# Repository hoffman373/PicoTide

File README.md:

# PicoTide

An ISA card that connects a Raspberry Pi Pico to an 8-bit ISA slot, so the Pico can see and drive the bus of a PC/XT-class machine. With the firmware in [`firmware/`](firmware/), the card serves an option ROM, such as the XTIDE Universal BIOS, to the machine.

## Overview

The ISA bus runs at 5 V and the Pico's GPIO is 3.3 V, so every signal between them passes through a level translator.

- **MCU:** Raspberry Pi Pico. The footprint is the Pico W's and takes any Pico-footprint board; the firmware targets the Pico 2 (RP2350).
- **Level translation:** SN74LVC8T245 8-bit dual-supply transceivers (3.3 V Pico side, 5 V ISA side)
- **Glue logic:** 74LVC1G02 / 74LVC1G04 / 74LVC1G06 single gates. The NOR gates combine SMEMR# and SMEMW# with AEN into `VALID_READ` and `VALID_WRITE`.
- **Bus connector:** 8-bit ISA edge connector (`Bus_ISA_8bit`)

### Pin mapping

| Pico GPIO | ISA signal | Net label |
|---|---|---|
| GPIO0-7 | A0-A7 and D0-D7, multiplexed | `P_A0_D0` ... `P_A7_D7` |
| GPIO8-15 | A8-A15 | `P_A8` ... `P_A15` |
| GPIO16-19 | A16-A19 | `P_A16` ... `P_A19` |
| GPIO20 | IO CH RDY (high pulls it low) | `P_IO_CHRDY` |
| GPIO21 | RESET DRV | `P_RESET` |
| GPIO22 | Address/data select | `P_ADR_DATA` |
| GPIO26 | Data translator direction | `P_DATA_DIR` |
| GPIO27 | NOR(SMEMW#, AEN) | `VALID_WRITE` |
| GPIO28 | NOR(SMEMR#, AEN) | `VALID_READ` |

Address and data share GPIO0-7. Each of those GPIOs goes through one translator to the matching address line and through another to the matching data line. `P_ADR_DATA` picks which translator owns them: high enables the address translator, low enables the data translator, and `P_DATA_DIR` then sets whether data flows from the Pico to the bus or the other way.

`IO_CHRDY` (ISA IO CH RDY) is driven through a 74LVC1G06 open-drain output so the Pico can insert wait states without driving the line high.

Net labels use a `P_` prefix for the Pico side of a translator. The matching ISA-side labels carry the bare ISA name.

## Opening the project

1. Install [KiCad](https://www.kicad.org/) 10 or newer. The files use the KiCad 10 format and will not open in older versions.
2. Clone the repository:
   ```
   git clone https://github.com/hoffman373/PicoTide.git
   ```
3. Open `PicoTide.kicad_pro`.

Custom footprints live in `lib/footprints/` and are registered through the project's `fp-lib-table` using `${KIPRJMOD}`, so no library setup is needed. Everything else uses stock KiCad symbols and footprints.

## Firmware

The [`firmware/`](firmware/) directory builds three firmwares for the card: a bench tester for a newly built card, a bus logger that shows where a BIOS scans for option ROMs, and an option ROM server. See [`firmware/README.md`](firmware/README.md) for building and using them.

## Notes

- **Bus timing:** at 4.77 MHz, a Pico 2 polling the bus from RAM on its second core answers memory reads in software with time to spare, without PIO or wait states. The option ROM server has booted an XT from the XTIDE Universal BIOS this way. `IO_CHRDY` is there for faster machines or slower responses.

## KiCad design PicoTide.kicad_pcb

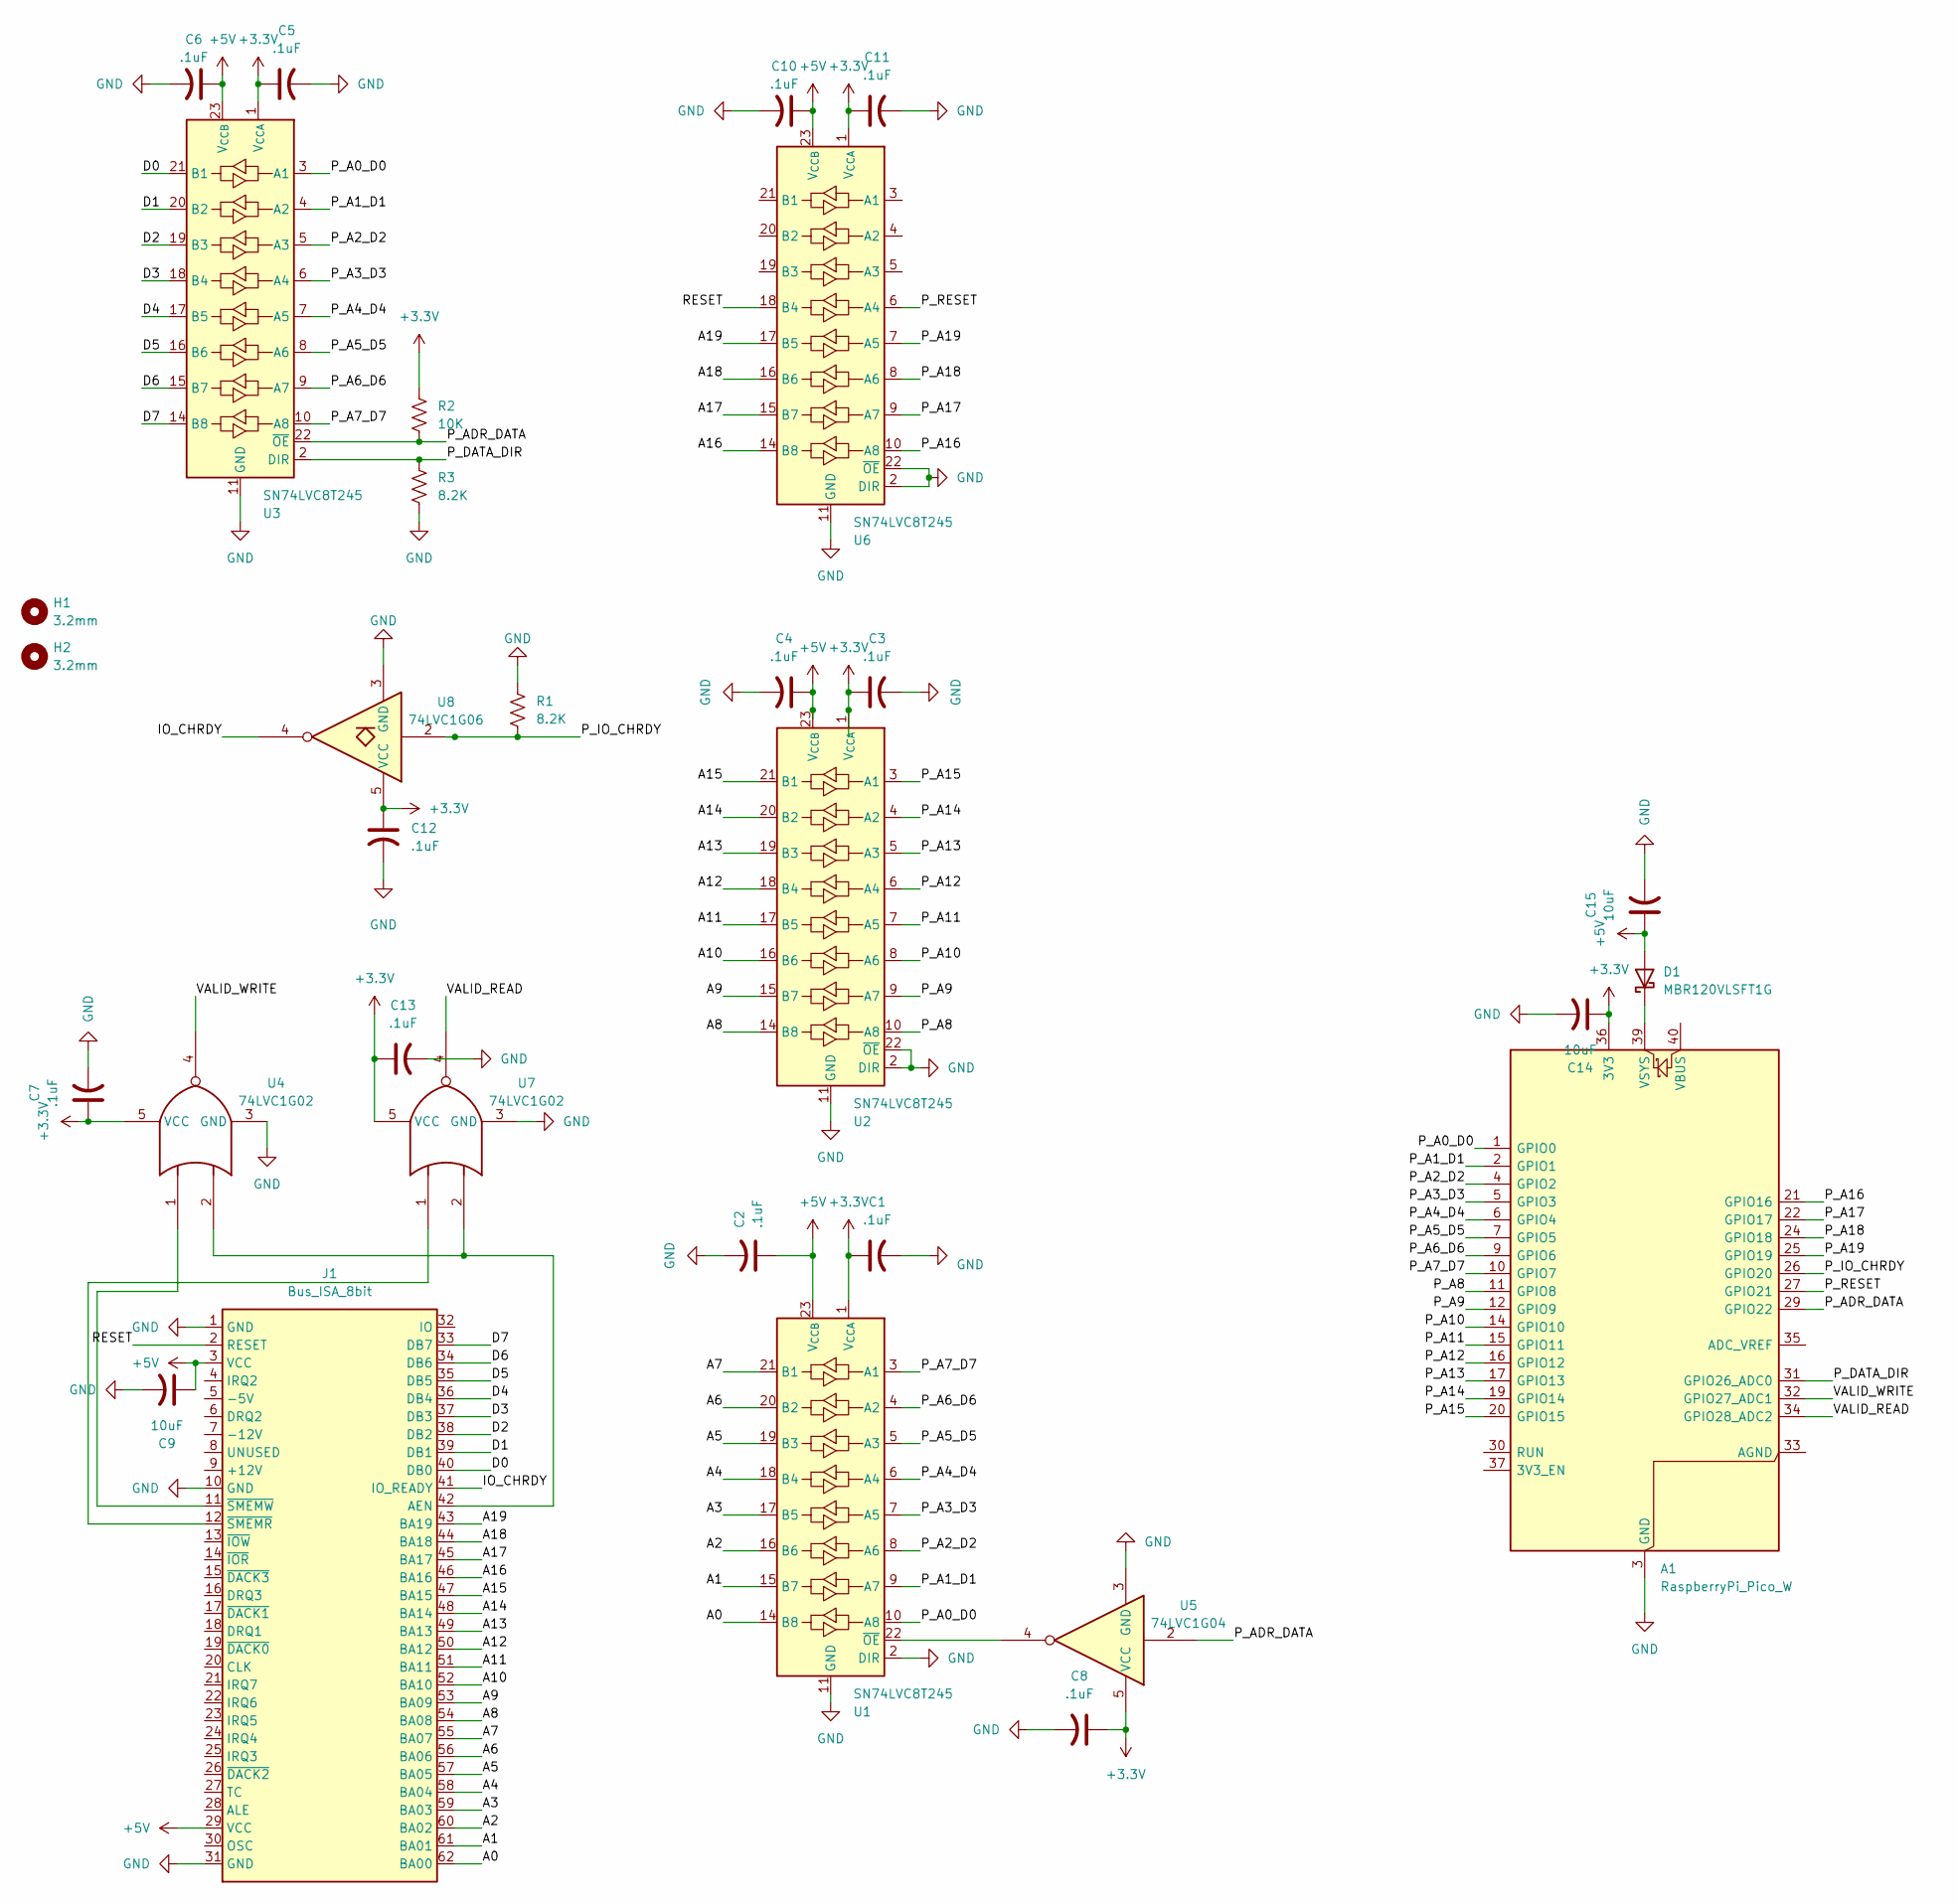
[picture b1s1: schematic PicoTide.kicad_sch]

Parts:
A1: RaspberryPi_Pico_W; RaspberryPi_Pico_MountingHole
C1, C2, C3, C4, C5, C6, C7, C8, C10, C11, C12, C13: .1uF; C_0805_2012Metric_Pad1.18x1.45mm_HandSolder
C9, C14, C15: 10uF; C_1206_3216Metric_Pad1.33x1.80mm_HandSolder
D1: MBR120VLSFT1G; D_SOD-123F
H1, H2: 3.2mm; MountingHole_3.2mm_M3
J1: Bus_ISA_8bit; PC_AT_8BIT
R1, R3: 8.2K; R_0805_2012Metric_Pad1.20x1.40mm_HandSolder
R2: 10K; R_0805_2012Metric_Pad1.20x1.40mm_HandSolder
U1, U2, U3, U6: SN74LVC8T245; SOIC-24W_7.5x15.4mm_P1.27mm
U4, U7: 74LVC1G02; SOT-23-5_HandSoldering
U5: 74LVC1G04; SOT-23-5_HandSoldering
U8: 74LVC1G06; SOT-23-5_HandSoldering

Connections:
+3.3V: A1.36 (3V3), C1.1, C3.1, C5.1, C7.1, C8.1, C11.1, C12.1, C13.1, C14.1, R2.1, U1.1 (V_{CCA}), U2.1 (V_{CCA}), U3.1 (V_{CCA}), U4.5 (VCC), U5.5 (VCC), U6.1 (V_{CCA}), U7.5 (VCC), U8.5 (VCC)
+5V: C2.1, C4.1, C6.1, C9.1, C10.1, C15.1, D1.2 (A), J1.3 (VCC), J1.29 (VCC), U1.23 (V_{CCB}), U1.24 (V_{CCB}), U2.23 (V_{CCB}), U2.24 (V_{CCB}), U3.23 (V_{CCB}), U3.24 (V_{CCB}), U6.23 (V_{CCB}), U6.24 (V_{CCB})
/A0: J1.62 (BA00), U1.14 (B8)
/A1: J1.61 (BA01), U1.15 (B7)
/A2: J1.60 (BA02), U1.16 (B6)
/A3: J1.59 (BA03), U1.17 (B5)
/A4: J1.58 (BA04), U1.18 (B4)
/A5: J1.57 (BA05), U1.19 (B3)
/A6: J1.56 (BA06), U1.20 (B2)
/A7: J1.55 (BA07), U1.21 (B1)
/A8: J1.54 (BA08), U2.14 (B8)
/A9: J1.53 (BA09), U2.15 (B7)
/A10: J1.52 (BA10), U2.16 (B6)
/A11: J1.51 (BA11), U2.17 (B5)
/A12: J1.50 (BA12), U2.18 (B4)
/A13: J1.49 (BA13), U2.19 (B3)
/A14: J1.48 (BA14), U2.20 (B2)
/A15: J1.47 (BA15), U2.21 (B1)
/A16: J1.46 (BA16), U6.14 (B8)
/A17: J1.45 (BA17), U6.15 (B7)
/A18: J1.44 (BA18), U6.16 (B6)
/A19: J1.43 (BA19), U6.17 (B5)
/D0: J1.40 (DB0), U3.21 (B1)
/D1: J1.39 (DB1), U3.20 (B2)
/D2: J1.38 (DB2), U3.19 (B3)
/D3: J1.37 (DB3), U3.18 (B4)
/D4: J1.36 (DB4), U3.17 (B5)
/D5: J1.35 (DB5), U3.16 (B6)
/D6: J1.34 (DB6), U3.15 (B7)
/D7: J1.33 (DB7), U3.14 (B8)
/IO_CHRDY: J1.41 (IO_READY), U8.4
/P_A0_D0: A1.1 (GPIO0), U1.10 (A8), U3.3 (A1)
/P_A1_D1: A1.2 (GPIO1), U1.9 (A7), U3.4 (A2)
/P_A2_D2: A1.4 (GPIO2), U1.8 (A6), U3.5 (A3)
/P_A3_D3: A1.5 (GPIO3), U1.7 (A5), U3.6 (A4)
/P_A4_D4: A1.6 (GPIO4), U1.6 (A4), U3.7 (A5)
/P_A5_D5: A1.7 (GPIO5), U1.5 (A3), U3.8 (A6)
/P_A6_D6: A1.9 (GPIO6), U1.4 (A2), U3.9 (A7)
/P_A7_D7: A1.10 (GPIO7), U1.3 (A1), U3.10 (A8)
/P_A8: A1.11 (GPIO8), U2.10 (A8)
/P_A9: A1.12 (GPIO9), U2.9 (A7)
/P_A10: A1.14 (GPIO10), U2.8 (A6)
/P_A11: A1.15 (GPIO11), U2.7 (A5)
/P_A12: A1.16 (GPIO12), U2.6 (A4)
/P_A13: A1.17 (GPIO13), U2.5 (A3)
/P_A14: A1.19 (GPIO14), U2.4 (A2)
/P_A15: A1.20 (GPIO15), U2.3 (A1)
/P_A16: A1.21 (GPIO16), U6.10 (A8)
/P_A17: A1.22 (GPIO17), U6.9 (A7)
/P_A18: A1.24 (GPIO18), U6.8 (A6)
/P_A19: A1.25 (GPIO19), U6.7 (A5)
/P_ADR_DATA: A1.29 (GPIO22), R2.2, U3.22 (~OE), U5.2
/P_DATA_DIR: A1.31 (GPIO26_ADC0), R3.1, U3.2 (DIR)
/P_IO_CHRDY: A1.26 (GPIO20), R1.2, U8.2
/P_RESET: A1.27 (GPIO21), U6.6 (A4)
/RESET: J1.2 (RESET), U6.18 (B4)
/VALID_READ: A1.34 (GPIO28_ADC2), U7.4
/VALID_WRITE: A1.32 (GPIO27_ADC1), U4.4
GND: A1.3 (GND), A1.8 (GND), A1.13 (GND), A1.18 (GND), A1.23 (GND), A1.28 (GND), A1.38 (GND), C1.2, C2.2, C3.2, C4.2, C5.2, C6.2, C7.2, C8.2, C9.2, C10.2, C11.2, C12.2, C13.2, C14.2, C15.2, J1.1 (GND), J1.10 (GND), J1.31 (GND), R1.1, R3.2, U1.2 (DIR), U1.11 (GND), U1.12 (GND), U1.13 (GND), U2.2 (DIR), U2.11 (GND), U2.12 (GND), U2.13 (GND), U2.22 (~OE), U3.11 (GND), U3.12 (GND), U3.13 (GND), U4.3 (GND), U5.3 (GND), U6.2 (DIR), U6.11 (GND), U6.12 (GND), U6.13 (GND), U6.22 (~OE), U7.3 (GND), U8.3 (GND)
unnamed: A1.39 (VSYS), D1.1 (K)
unnamed: J1.42 (AEN), U4.2, U7.2
unnamed: J1.12 (~SMEMR), U7.1
unnamed: J1.11 (~SMEMW), U4.1
unnamed: U1.22 (~OE), U5.4

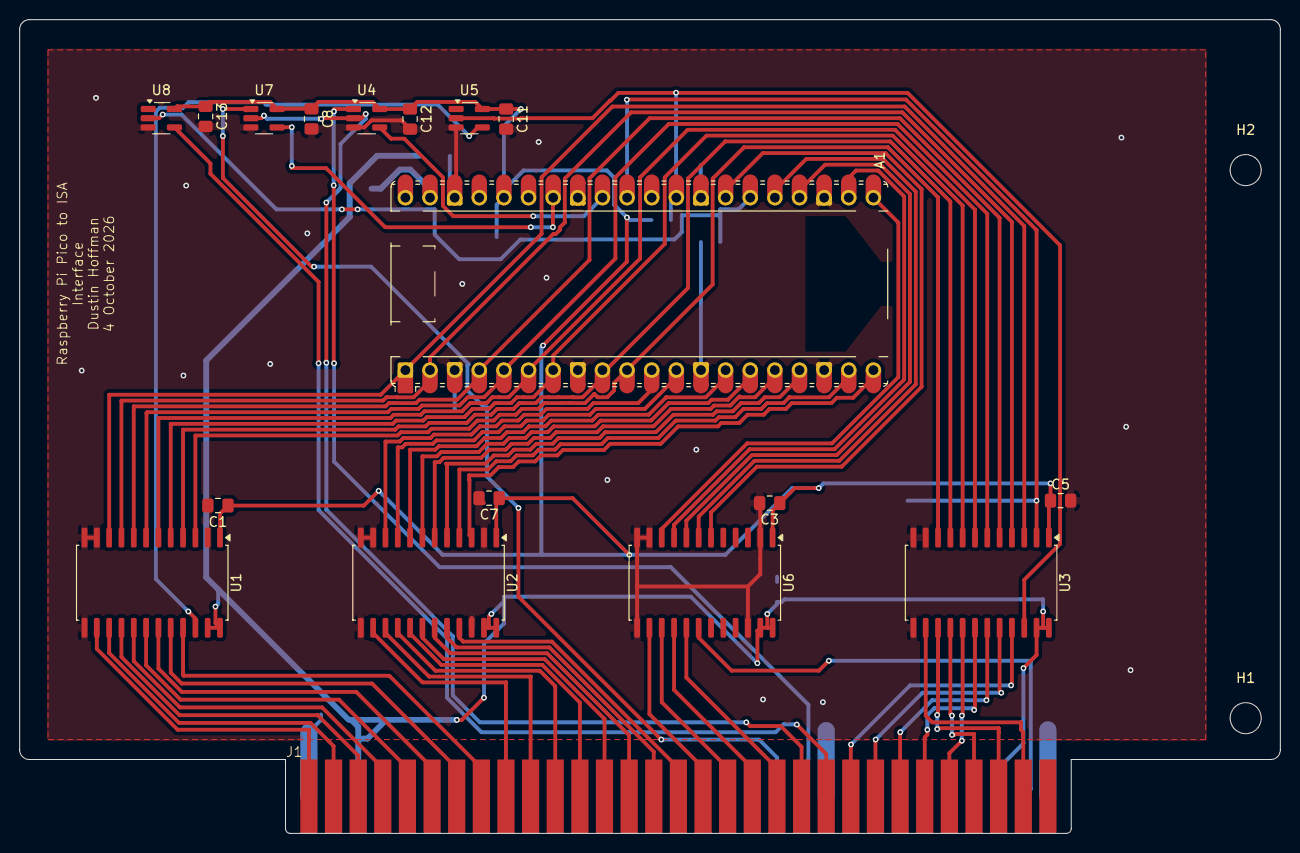
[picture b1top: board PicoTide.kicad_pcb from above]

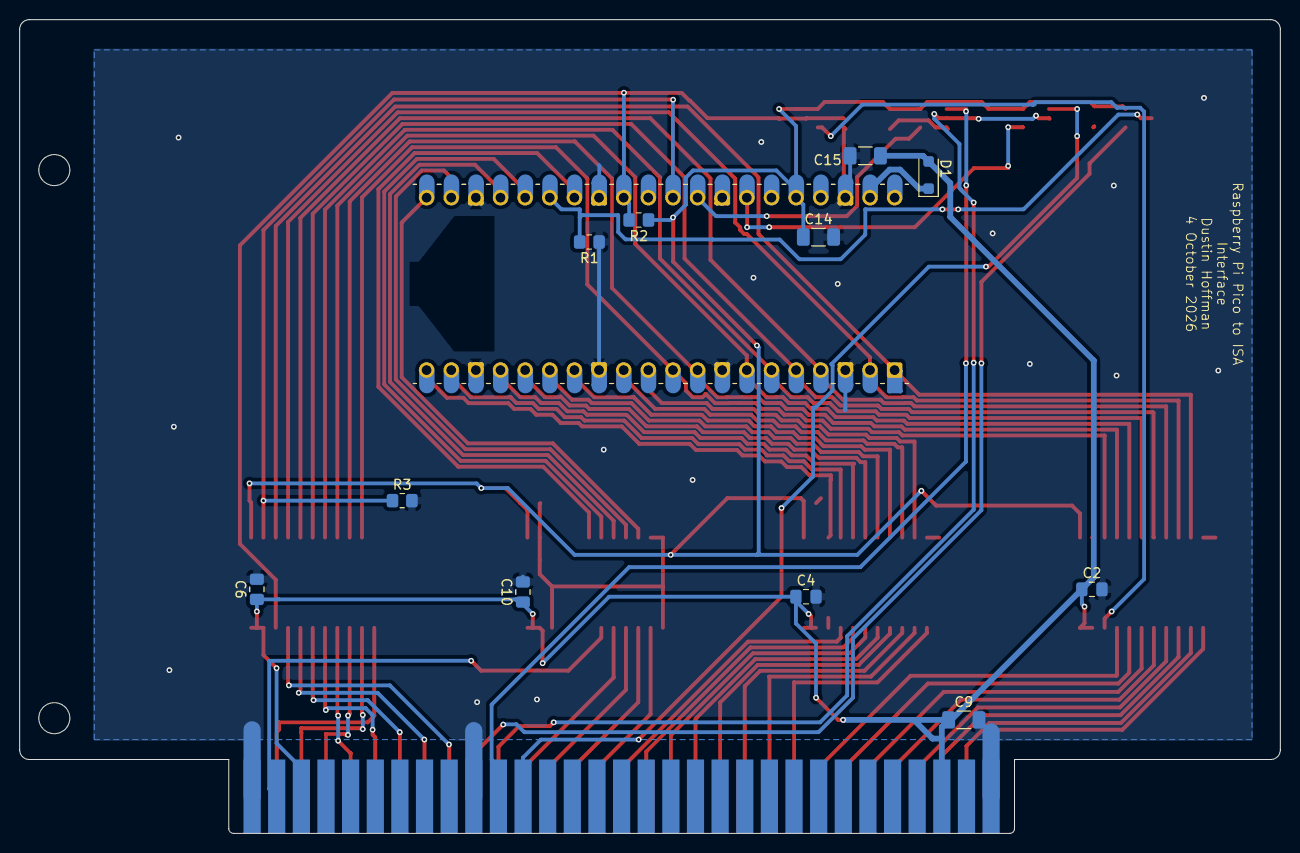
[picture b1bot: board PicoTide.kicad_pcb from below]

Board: 2 copper layers, 130.0 x 83.9 mm, 31 parts (11 on the bottom side), 64 nets.
